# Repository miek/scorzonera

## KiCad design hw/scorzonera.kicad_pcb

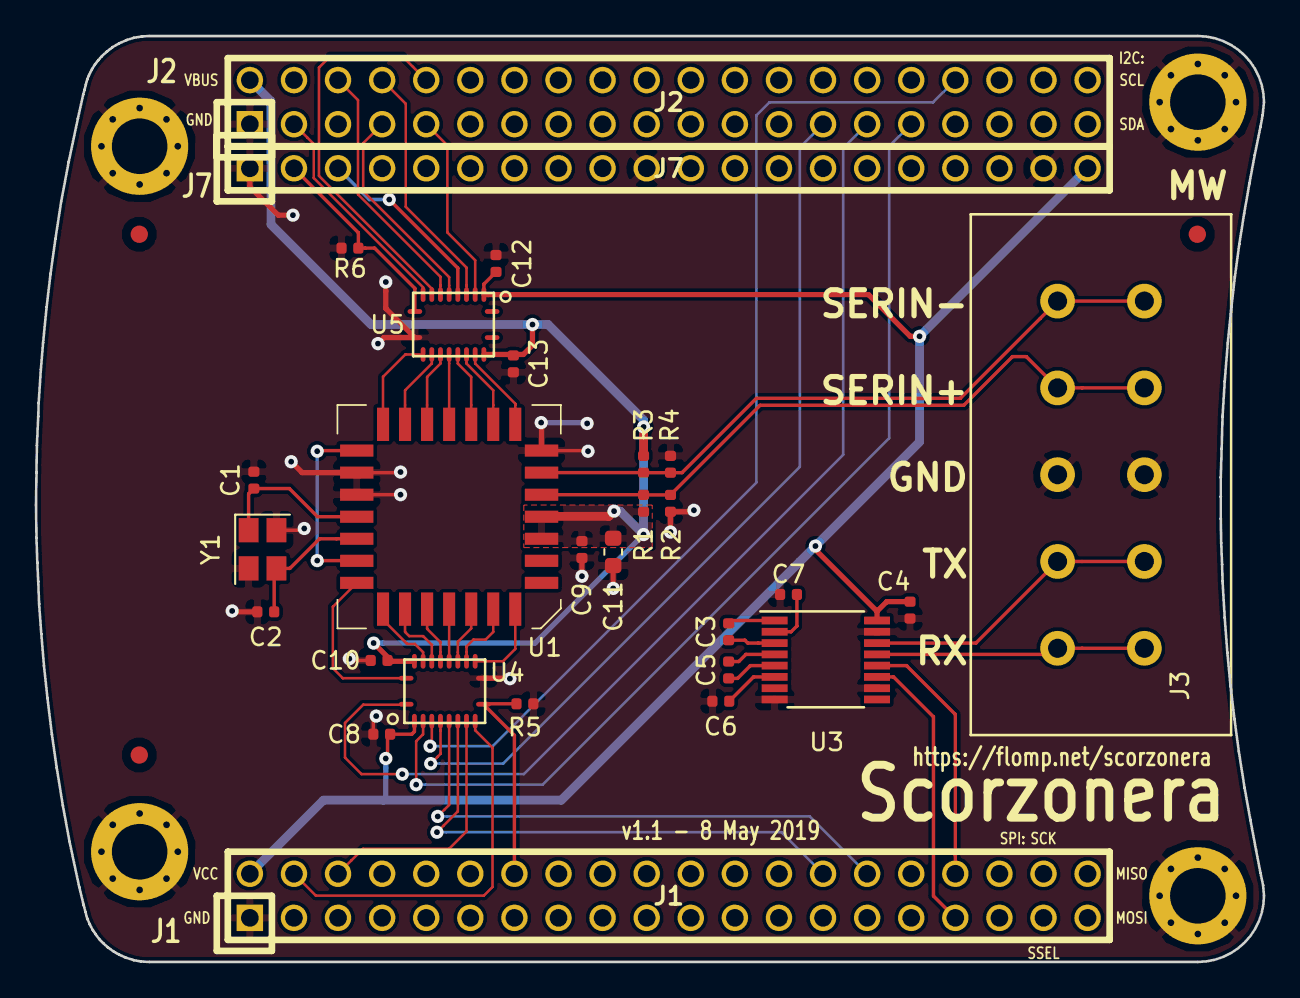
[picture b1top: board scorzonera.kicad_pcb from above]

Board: 2 copper layers, 70.7 x 53.3 mm, 35 parts (0 on the bottom side), 50 nets.

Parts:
C1, C2: 18p; C_0402_1005Metric
C3, C4, C5, C6, C7, C8, C9, C10, C12, C13: 100n; C_0402_1005Metric
C11: 1u; C_0603_1608Metric
FD1, FD2, FD3: Fiducial_1mm_Dia_2mm_Outer
J1: NEIGHBOR1; HEADER-2x20
J2: NEIGHBOR2; HEADER-2x20
J3: Conn_01x05; 256-743-5
J7: BONUS_ROW; HEADER-1x20
MH1, MH2, MH3, MH4: MOUNTING_HOLE; HOLE126MIL-COPPER
R1, R3: 120R; R_0402_1005Metric
R2, R4: 330R; R_0402_1005Metric
R5, R6: 10K; R_0402_1005Metric
U1: AM7969; PLCC-28
U3: MAX3232; TSSOP-16_4.4x5mm_P0.65mm
U4, U5: TXS0108EPW; Texas_R-PVQFN-N20_4.65x3.65x1mm
Y1: Crystal_GND24; Crystal_SMD_SeikoEpson_TSX3225-4Pin_3.2x2.5mm

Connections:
+5V: C9.1, C10.1, C11.1, C13.1, J2.2, R1.1, R3.1, U1.7, U1.8, U4.19, U5.19
/CLK: U1.19, U1.24
/CO0: U1.15, U5.15
/CO1: U1.16, U5.14
/CO2: U1.17, U5.13
/CO3: U1.18, U5.12
/CSTRB: U1.13, U5.17
/DO0: U1.4, U4.12
/DO1: U1.3, U4.13
/DO2: U1.2, U4.14
/DO3: U1.1, U4.15
/DO4: U1.28, U4.16
/DO5: U1.27, U4.17
/DO6: U1.26, U4.18
/DO7: U1.25, U4.20
/DSTRB: U1.12, U5.18
/P5_2: J1.14, R5.1, U4.10
/P6_4: J7.2, R6.1, U5.10
/P6_5: J7.3, U5.5
/RS232_RX: J3.1, U3.13
/RS232_TX: J3.2, U3.14
/SERIN+: J3.4, R1.2, R2.1, U1.9
/SERIN-: J3.5, R3.2, R4.1, U1.10
/SGPIO0: J1.4, U4.9
/SGPIO1: J1.6, U4.8
/SGPIO2: J1.28, U4.7
/SGPIO3: J1.30, U4.6
/SGPIO4: J2.27, U4.5
/SGPIO5: J2.34, U4.4
/SGPIO6: J2.31, U4.3
/SGPIO7: J2.29, U4.1
/SGPIO8: J2.8, U5.4
/SGPIO9: J2.9, U5.3
/SGPIO10: J2.7, U5.6
/SGPIO11: J2.6, U5.7
/SGPIO12: J2.10, U5.8
/SGPIO13: J2.3, U5.9
/U0_RXD: J1.34, U3.12
/U0_TXD: J1.33, U3.11
/VLTN: U1.14, U5.16
/X1: C1.1, U1.22, Y1.1
/X2: C2.1, U1.23, Y1.3
GND: C1.2, C2.2, C4.1, C6.1, C7.1, C8.2, C9.2, C10.2, C11.2, C12.2, C13.2, J1.1, J2.1, J3.3, J7.1, J7.10, J7.19, MH1.1, MH2.1, MH3.1, MH4.1, R2.2, R4.2, R5.2, R6.2, U1.11, U1.20, U1.21, U3.8, U3.10, U3.15, U4.11, U5.11, Y1.2, Y1.4
unnamed: C3.1, U3.1
unnamed: C3.2, U3.3
unnamed: C5.1, U3.4
unnamed: C5.2, U3.5
unnamed: C6.2, U3.6
unnamed: C7.2, U3.2
VCC: C4.2, C8.1, C12.1, J1.2, J7.20, U3.16, U4.2, U5.2

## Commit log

2019-05-05 init. copy neighbour-template from greatfet-hardware
2019-05-05 Switch to 2 layer
2019-05-05 Update silk
2019-05-05 Fix up schematic libs & symbols
2019-05-05 Set schematic sheet info
2019-05-05 Add AM7969 symbol
2019-05-05 Some wiring
2019-05-05 Map out remaining SGPIO, add SERIN dividers, etc.
2019-05-06 Level translator and some routing
2019-05-06 Routed! for now
2019-05-06 RS232
2019-05-07 Add Wago connector, more routing
2019-05-07 Switch to 2 level shifters, caps, route, silk
2019-05-08 Fix up fab layer
2019-05-08 Fiducials
2019-05-08 Connect OEs & add pulldowns, more silk, random cleanup
2019-06-06 Host boilerplate
2019-06-08 Receive some data over USB
2019-06-08 Some basic video display
2019-06-09 Tidy up buffer allocation & add some nicer error handling
2019-06-09 Break out frame sync to module, tidy up, make work
2019-06-12 Exit on Q too
2019-06-12 Build a LUT for level/gain & add adjustment
2019-06-13 Colors!
2019-08-14 Cleanup
2019-08-14 Switch to palette for color maps
2019-08-18 Convert color maps from `scarlet`
2021-03-07 Stream from luna hardware
2021-03-14 Add pause feature
2021-03-14 Update for new FPGA frame sync
2021-03-14 Remove old code for greatfet neighbour
2021-03-14 Add gateware
2021-03-14 gateware: Remove uses of Past/Rose/Fell, fixes CDR tests
2021-03-14 gateware: tidy up taxi
2021-03-14 gateware: drop use of deprecated nmigen.back.pysim
2021-03-19 gateware: remove a magic number for sync
2021-07-04 Use one USB transfer per frame
2021-07-18 gateware: Port to LUNA hardware
2021-07-18 gateware: borrow acm.py from LUNA
2021-07-20 gateware: working loopback serial
2021-07-21 gateware: tidy up names left in from example code
2021-07-21 gateware: add UART RX
2021-07-22 uart: flush stream on new-line character
2021-07-22 gateware: add UART TX
2021-07-22 gateware: fix ACM endpoint packet size
2022-03-05 Update upstream package naming
